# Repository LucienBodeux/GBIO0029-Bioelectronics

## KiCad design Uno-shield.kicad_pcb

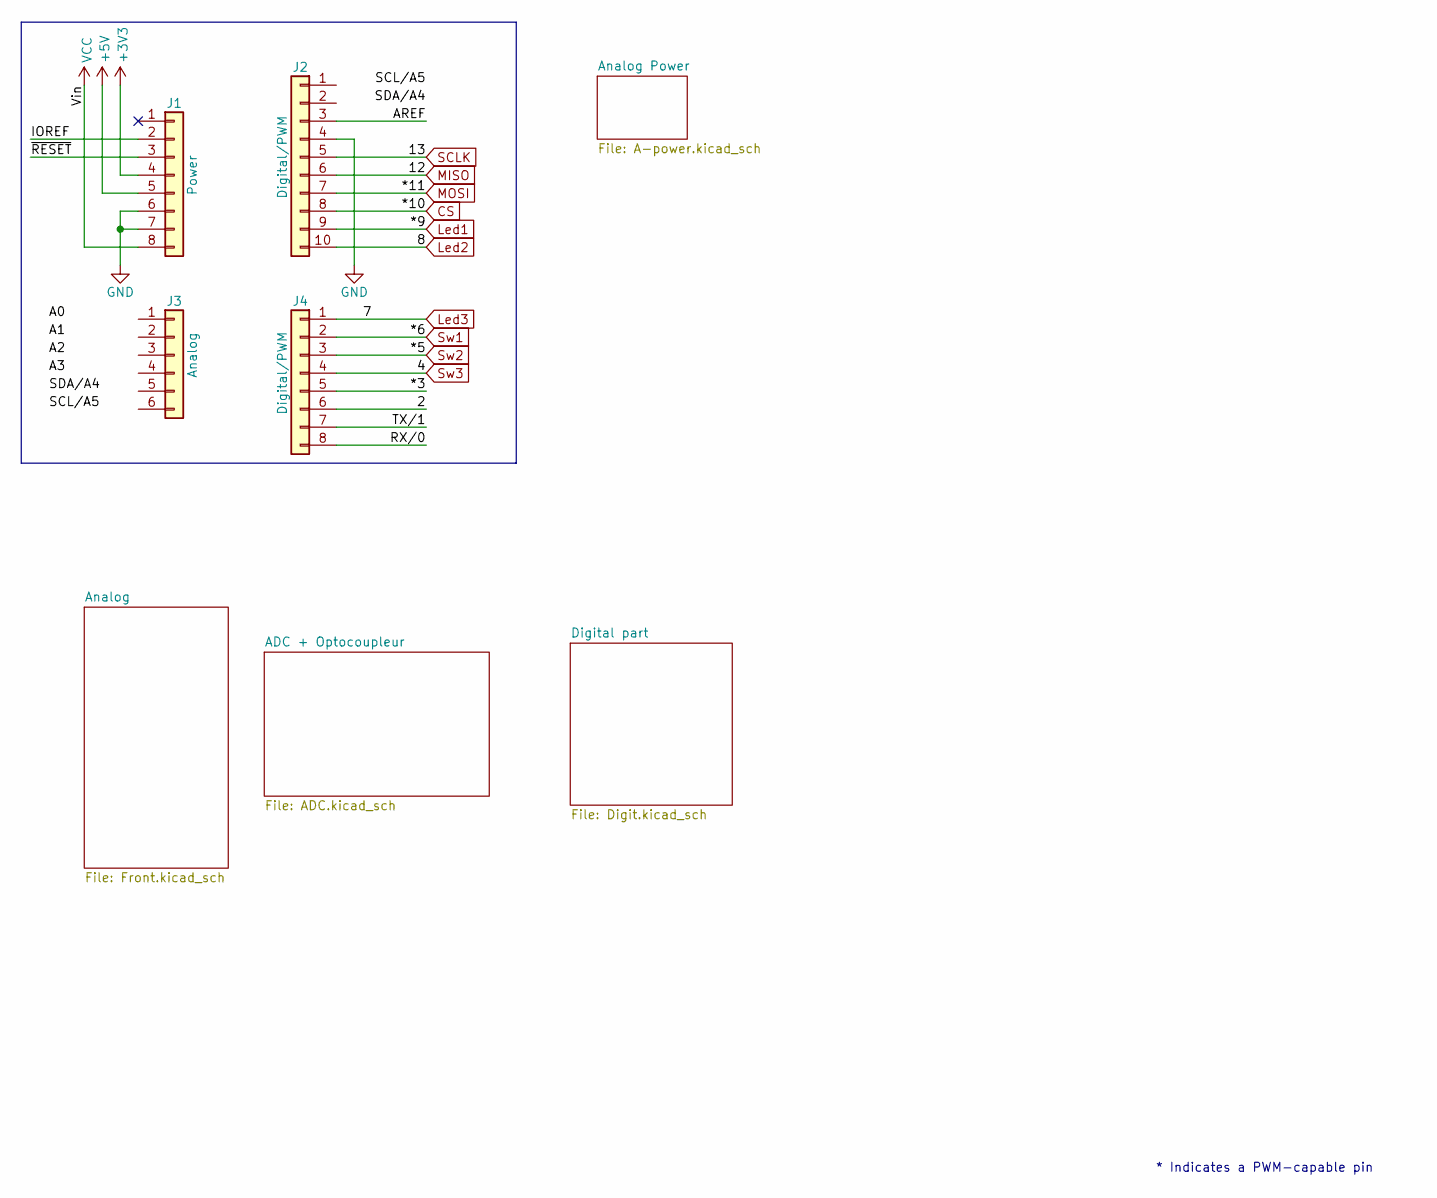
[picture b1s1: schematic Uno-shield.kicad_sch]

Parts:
J1: Power; PinSocket_1x08_P2.54mm_Vertical
J2: Digital/PWM; PinSocket_1x10_P2.54mm_Vertical
J3: Analog; PinSocket_1x06_P2.54mm_Vertical
J4: Digital/PWM; PinSocket_1x08_P2.54mm_Vertical

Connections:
+3V3: J1.4; also elsewhere on the board
+5V: J1.5; also elsewhere on the board
/2: J4.6
/*3: J4.5
/AREF: J2.3
/IOREF: J1.2
/RX/0: J4.8
/TX/1: J4.7
/~RESET: J1.3
CS: J2.8; also elsewhere on the board
GND: J1.6, J1.7, J2.4; also elsewhere on the board
Led1: J2.9; also elsewhere on the board
Led2: J2.10; also elsewhere on the board
Led3: J4.1; also elsewhere on the board
MISO: J2.6; also elsewhere on the board
MOSI: J2.7; also elsewhere on the board
SCLK: J2.5; also elsewhere on the board
Sw1: J4.2; also elsewhere on the board
Sw2: J4.3; also elsewhere on the board
Sw3: J4.4; also elsewhere on the board
VCC: J1.8

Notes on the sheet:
* Indicates a PWM-capable pin

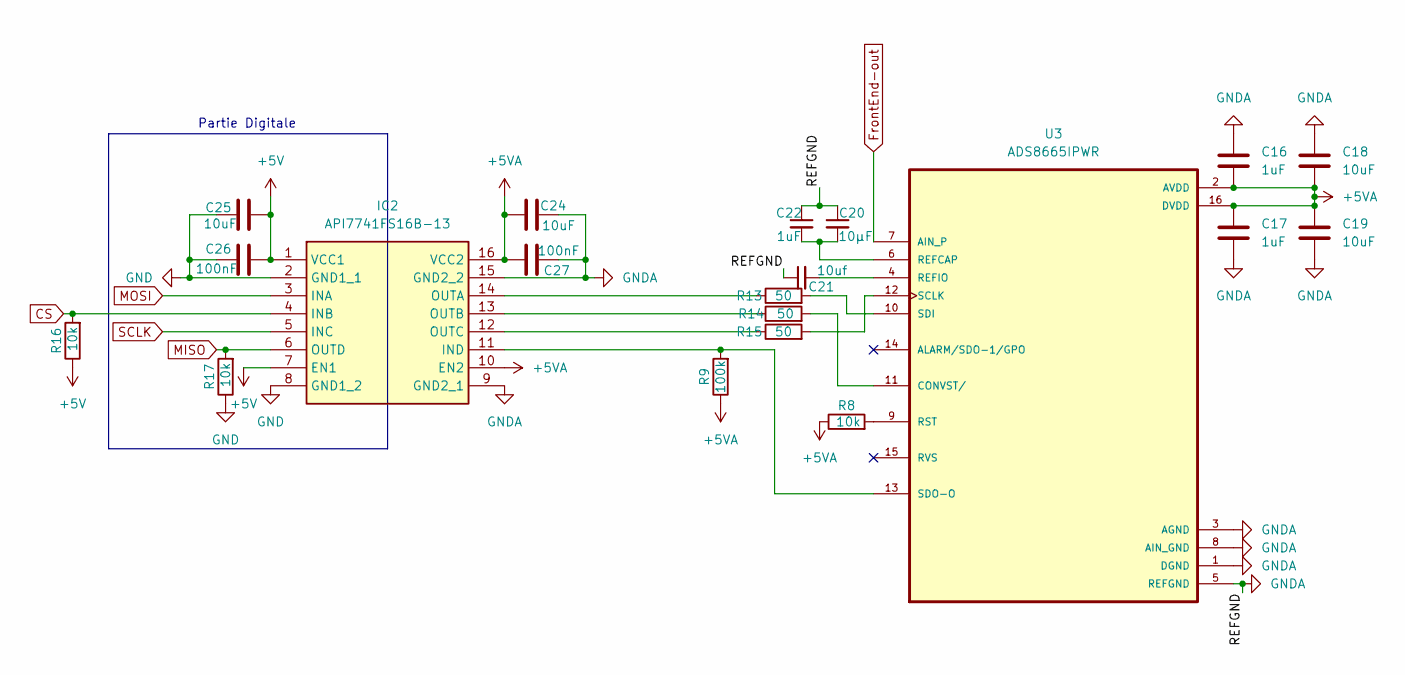
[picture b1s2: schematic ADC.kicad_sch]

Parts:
C16, C17, C22: 1uF; C_0805_2012Metric_Pad1.18x1.45mm_HandSolder
C18, C19, C24, C25: 10uF; C_1206_3216Metric_Pad1.33x1.80mm_HandSolder
C20: 10µF; C_1206_3216Metric_Pad1.33x1.80mm_HandSolder
C21: 10uf; C_1206_3216Metric_Pad1.33x1.80mm_HandSolder
C26, C27: 100nF; C_0805_2012Metric_Pad1.18x1.45mm_HandSolder
IC2: API7741FS16B-13; SOIC-16W_7.5x10.3mm_P1.27mm; Manufacturer_Part_Number API7741FS16B-13
R8, R16, R17: 10k; R_0805_2012Metric_Pad1.20x1.40mm_HandSolder
R9: 100k; R_0805_2012Metric_Pad1.20x1.40mm_HandSolder
R13, R14, R15: 50; R_0805_2012Metric_Pad1.20x1.40mm_HandSolder
U3: ADS8665IPWR; TSSOP-16_4.4x5mm_P0.65mm; MPN ADS8665IPWR

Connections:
+5V: C25.2, C26.2, IC2.1 (VCC1), IC2.7 (EN1), R16.1; also elsewhere on the board
+5VA: C16.2, C17.1, C18.2, C19.1, C24.1, C27.2, IC2.10 (EN2), IC2.16 (VCC2), R8.1, R9.1, U3.2 (AVDD), U3.16 (DVDD); also elsewhere on the board
CS: IC2.4 (INB), R16.2; also elsewhere on the board
FrontEnd-out: U3.7 (AIN_P); also elsewhere on the board
GND: C25.1, C26.1, IC2.2 (GND1_1), IC2.8 (GND1_2), R17.1; also elsewhere on the board
GNDA: C16.1, C17.2, C18.1, C19.2, C20.1, C21.1, C22.1, C24.2, C27.1, IC2.9 (GND2_1), IC2.15 (GND2_2), U3.1 (DGND), U3.3 (AGND), U3.5 (REFGND), U3.8 (AIN_GND); also elsewhere on the board
MISO: IC2.6 (OUTD), R17.2; also elsewhere on the board
MOSI: IC2.3 (INA); also elsewhere on the board
unnamed: IC2.11 (IND), R9.2, U3.13 (SDO-O)
unnamed: IC2.14 (OUTA), R13.1
unnamed: IC2.13 (OUTB), R14.1
unnamed: IC2.12 (OUTC), R15.1
unnamed: R14.2, U3.11 (CONVST/)
unnamed: C20.2, C22.2, U3.6 (REFCAP)
unnamed: C21.2, U3.4 (REFIO)
unnamed: R8.2, U3.9 (RST)
unnamed: R15.2, U3.12 (SCLK)
unnamed: R13.2, U3.10 (SDI)
SCLK: IC2.5 (INC); also elsewhere on the board

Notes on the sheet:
Partie Digitale

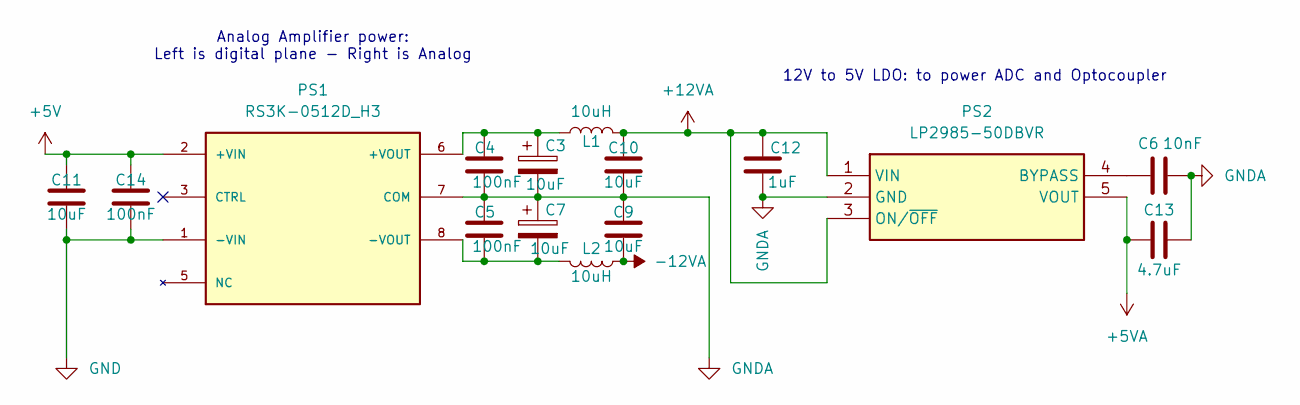
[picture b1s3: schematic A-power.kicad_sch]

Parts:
C3, C7, C9, C10, C11: 10uF; C_1206_3216Metric_Pad1.33x1.80mm_HandSolder
C4, C5, C14: 100nF; C_0805_2012Metric_Pad1.18x1.45mm_HandSolder
C6: 10nF; C_0805_2012Metric_Pad1.18x1.45mm_HandSolder
C12: 1uF; C_0805_2012Metric_Pad1.18x1.45mm_HandSolder
C13: 4.7uF; C_0805_2012Metric_Pad1.18x1.45mm_HandSolder
L1, L2: 10uH; L_Bourns-SRN4018
PS1: RS3K-0512D_H3; Converter_DCDC_TRACO_TEC2-12xxWI_24xxWI_48xxWI_THT; MPN RS3K-0512D/H3; DigiKey_Part_Number 945-RS3K-0512D/H3-ND
PS2: LP2985-50DBVR; SOT-23-5_HandSoldering; Mouser Part Number 595-LP2985-50DBVR

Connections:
+5V: C11.1, C14.1, PS1.2 (+VIN); also elsewhere on the board
+5VA: C13.1, PS2.5 (VOUT); also elsewhere on the board
+12VA: C10.1, C12.1, L1.2, PS2.1 (VIN), PS2.3 (ON/~OFF); also elsewhere on the board
-12VA: C9.2, L2.1; also elsewhere on the board
GND: C11.2, C14.2, PS1.1 (-VIN); also elsewhere on the board
GNDA: C3.2, C4.1, C5.2, C6.2, C7.1, C9.1, C10.2, C12.2, C13.2, PS1.7 (COM), PS2.2 (GND); also elsewhere on the board
unnamed: C3.1, C4.2, L1.1, PS1.6 (+VOUT)
unnamed: C5.1, C7.2, L2.2, PS1.8 (-VOUT)
unnamed: C6.1, PS2.4 (BYPASS)

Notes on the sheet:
12V to 5V LDO: to power ADC and Optocoupler
Analog Amplifier power: Left is digital plane - Right is Analog

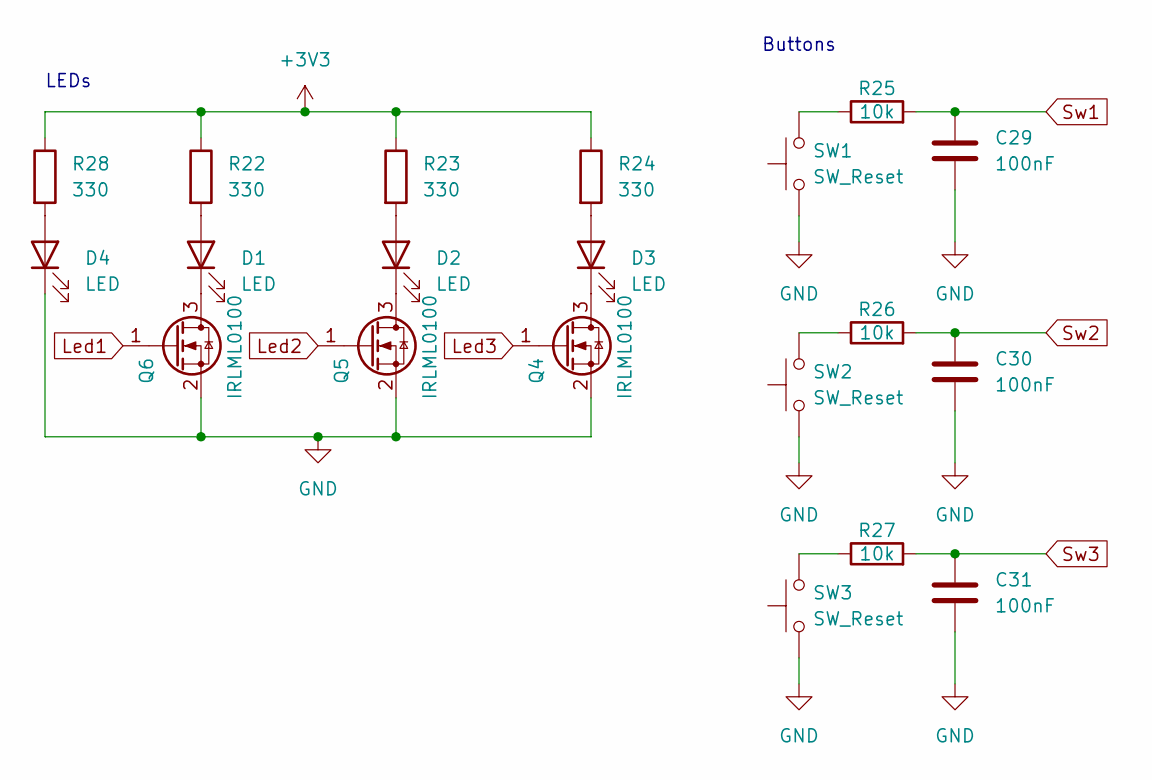
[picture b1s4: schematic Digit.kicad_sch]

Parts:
C29, C30, C31: 100nF; C_0805_2012Metric_Pad1.18x1.45mm_HandSolder
D1, D2, D3, D4: LED; LED_0805_2012Metric_Pad1.15x1.40mm_HandSolder
Q4, Q5, Q6: IRLML0100; SOT-23
R22, R23, R24, R28: 330; R_0805_2012Metric_Pad1.20x1.40mm_HandSolder
R25, R26, R27: 10k; R_0805_2012Metric_Pad1.20x1.40mm_HandSolder
SW1, SW2, SW3: SW_Reset; SW_PUSH_6mm

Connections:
+3V3: R22.1, R23.1, R24.1, R28.1; also elsewhere on the board
GND: C29.2, C30.2, C31.2, D4.1 (K), Q4.2 (S), Q5.2 (S), Q6.2 (S), SW1.1, SW2.1, SW3.1; also elsewhere on the board
Led1: Q6.1 (G); also elsewhere on the board
Led2: Q5.1 (G); also elsewhere on the board
Led3: Q4.1 (G); also elsewhere on the board
unnamed: D1.2 (A), R22.2
unnamed: D1.1 (K), Q6.3 (D)
unnamed: D2.2 (A), R23.2
unnamed: D2.1 (K), Q5.3 (D)
unnamed: D3.2 (A), R24.2
unnamed: D3.1 (K), Q4.3 (D)
unnamed: D4.2 (A), R28.2
unnamed: R25.1, SW1.2
unnamed: R26.1, SW2.2
unnamed: R27.1, SW3.2
Sw1: C29.1, R25.2; also elsewhere on the board
Sw2: C30.1, R26.2; also elsewhere on the board
Sw3: C31.1, R27.2; also elsewhere on the board

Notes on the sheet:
LEDs
Buttons

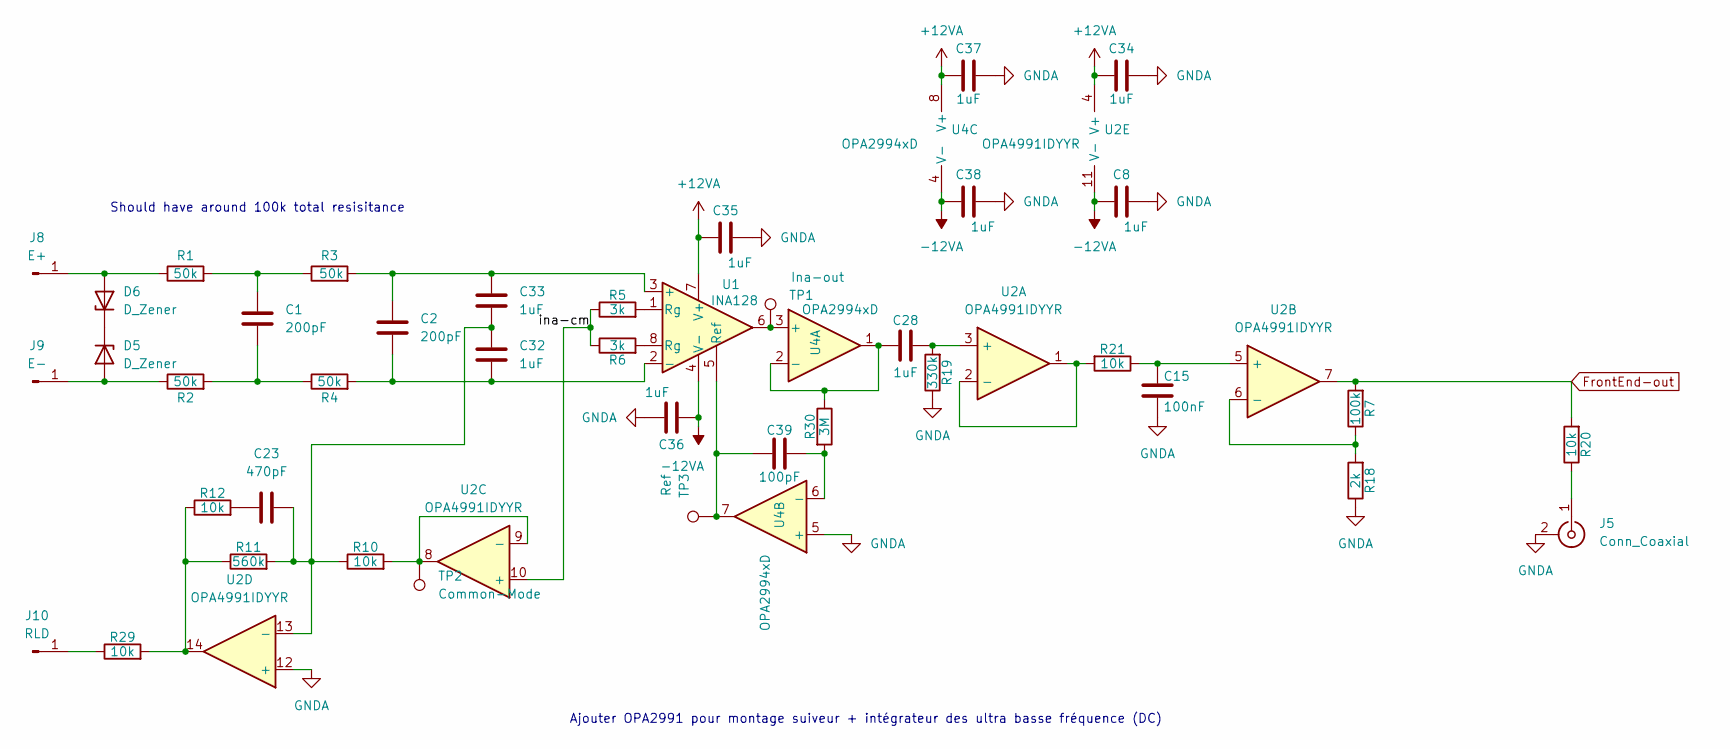
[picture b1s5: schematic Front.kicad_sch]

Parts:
C1, C2: 200pF; C_0805_2012Metric_Pad1.18x1.45mm_HandSolder
C8, C28, C32, C33, C34, C35, C36, C37, C38: 1uF; C_0805_2012Metric_Pad1.18x1.45mm_HandSolder
C15: 100nF; C_1206_3216Metric_Pad1.33x1.80mm_HandSolder
C23: 470pF; C_0805_2012Metric_Pad1.18x1.45mm_HandSolder
C39: 100pF; C_0805_2012Metric_Pad1.18x1.45mm_HandSolder
D5, D6: D_Zener; D_SMA_Handsoldering
J5: Conn_Coaxial; 031532951RFX
J8: E+; MountingHole_3.5mm_Pad_TopOnly
J9: E-; MountingHole_3.5mm_Pad_TopOnly
J10: RLD; MountingHole_3.5mm_Pad_TopOnly
R1, R2, R3, R4: 50k; R_0805_2012Metric_Pad1.20x1.40mm_HandSolder
R5, R6: 3k; R_0805_2012Metric_Pad1.20x1.40mm_HandSolder
R7: 100k; R_0805_2012Metric_Pad1.20x1.40mm_HandSolder
R10, R12, R20, R21, R29: 10k; R_0805_2012Metric_Pad1.20x1.40mm_HandSolder
R11: 560k; R_0805_2012Metric_Pad1.20x1.40mm_HandSolder
R18: 2k; R_0805_2012Metric_Pad1.20x1.40mm_HandSolder
R19: 330k; R_0805_2012Metric_Pad1.20x1.40mm_HandSolder
R30: 3M; R_0805_2012Metric_Pad1.20x1.40mm_HandSolder
TP1: Ina-out; TestPoint_Pad_D2.0mm
TP2: Common-Mode; TestPoint_Pad_D2.0mm
TP3: Ref; TestPoint_Pad_D2.0mm
U1: INA128; SOIC-8_3.9x4.9mm_P1.27mm
U2: OPA4991IDYYR; SOIC-14_3.9x8.7mm_P1.27mm
U4: OPA2994xD; SOIC-8_3.9x4.9mm_P1.27mm

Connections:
+12VA: C34.1, C35.1, C37.1, U1.7 (V+), U2.4 (V+), U4.8 (V+); also elsewhere on the board
-12VA: C8.1, C36.1, C38.1, U1.4 (V-), U2.11 (V-), U4.4 (V-); also elsewhere on the board
/Analog/ina-cm: R5.1, R6.1, U2.10 (+)
FrontEnd-out: R7.2, R20.2, U2.7; also elsewhere on the board
GNDA: C8.2, C15.1, C34.2, C35.2, C36.2, C37.2, C38.2, J5.2 (Ext), R18.1, R19.1, U2.12 (+), U4.5 (+); also elsewhere on the board
unnamed: C1.1, R1.2, R3.1
unnamed: C1.2, R2.2, R4.1
unnamed: C23.2, R12.2
unnamed: D5.2 (A), J9.1 (Pin_1_1), R2.1
unnamed: D5.1 (K), D6.1 (K)
unnamed: D6.2 (A), J8.1 (Pin_1_1), R1.1
unnamed: J5.1 (In), R20.1
unnamed: J10.1 (Pin_1_1), R29.1
unnamed: R5.2, U1.1 (Rg)
unnamed: R6.2, U1.8 (Rg)
unnamed: R11.1, R12.1, R29.2, U2.14
unnamed: C2.1, C33.1, R3.2, U1.3 (+)
unnamed: C2.2, C32.2, R4.2, U1.2 (-)
unnamed: C39.1, TP3.1 (1_1), U1.5 (Ref), U4.7
unnamed: C28.2, R19.2, U2.3 (+)
unnamed: R21.2, U2.1, U2.2 (-)
unnamed: C15.2, R21.1, U2.5 (+)
unnamed: R7.1, R18.2, U2.6 (-)
unnamed: R10.2, TP2.1 (1_1), U2.8, U2.9 (-)
unnamed: C23.1, C32.1, C33.2, R10.1, R11.2, U2.13 (-)
unnamed: TP1.1 (1_1), U1.6, U4.3 (+)
unnamed: C28.1, R30.1, U4.1, U4.2 (-)
unnamed: C39.2, R30.2, U4.6 (-)

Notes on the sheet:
Ajouter OPA2991 pour montage suiveur + intégrateur des ultra basse fréquence (DC)
Should have around 100k total resisitance

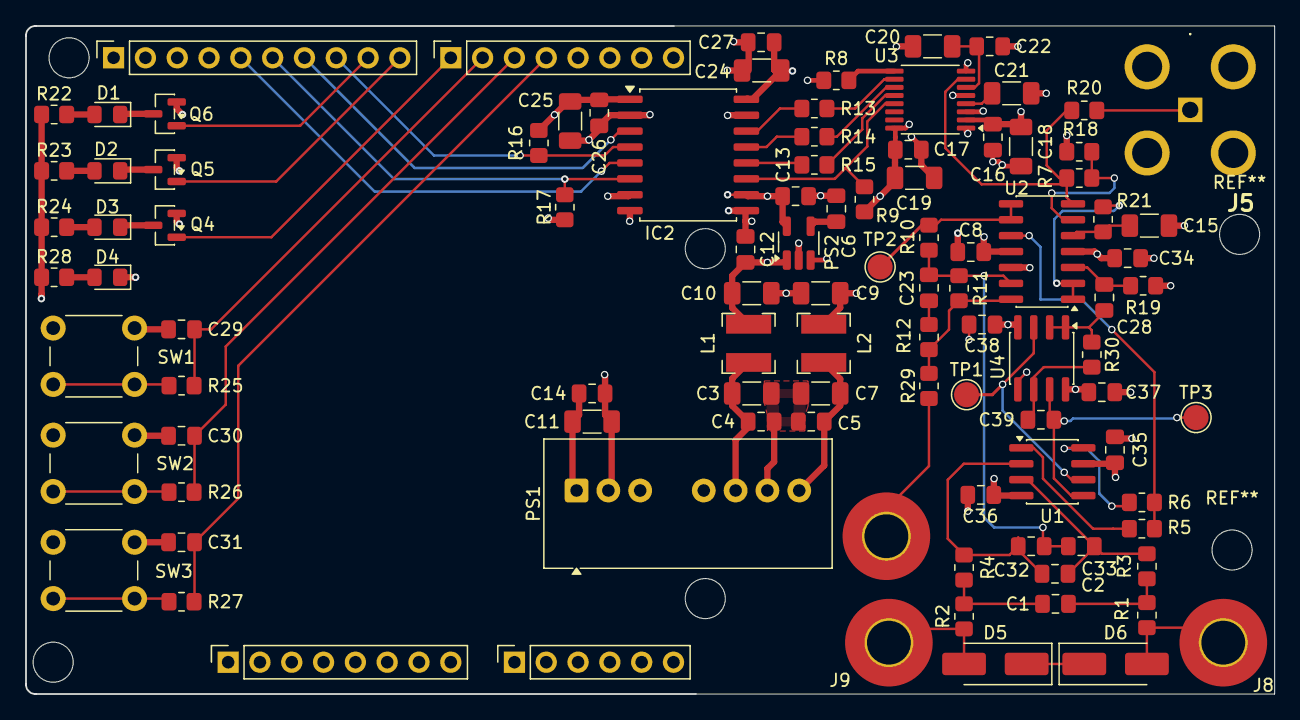
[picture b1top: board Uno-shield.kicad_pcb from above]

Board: 4 copper layers, 99.7 x 53.3 mm, 105 parts (0 on the bottom side), 65 nets.

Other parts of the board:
MH1, MH2, MH3, MH4: MountingHole_3.2mm

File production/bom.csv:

Designator,Footprint,Quantity,Value,LCSC Part #
"C1, C2",0805,2,200pF,
"C10, C11, C18, C19, C21, C24, C25, C3, C7, C9",1206,10,10uF,
"C12, C16, C17, C22, C28, C32, C33, C34, C35, C36, C37, C38, C8",0805,13,1uF,
C13,0805,1,4.7uF,
"C14, C26, C27, C29, C30, C31, C4, C5",0805,8,100nF,
C15,1206,1,100nF,
C20,1206,1,10µF,
C23,0805,1,470pF,
C39,0805,1,100pF,
C6,0805,1,10nF,
"D1, D2, D3, D4",0805,4,LED,
"D5, D6",D_SMA_Handsoldering,2,D_Zener,
IC2,SOIC-16W_7.5x10.3mm_P1.27mm,1,API7741FS16B-13,
J1,PinSocket_1x08_P2.54mm_Vertical,1,Power,
J10,MountingHole_3.5mm_Pad_TopOnly,1,RLD,
J2,PinSocket_1x10_P2.54mm_Vertical,1,Digital/PWM,
J3,PinSocket_1x06_P2.54mm_Vertical,1,Analog,
J4,PinSocket_1x08_P2.54mm_Vertical,1,Digital/PWM,
J5,031532951RFX,1,Conn_Coaxial,
J8,MountingHole_3.5mm_Pad_TopOnly,1,E+,
J9,MountingHole_3.5mm_Pad_TopOnly,1,E-,
"L1, L2",L_Bourns-SRN4018,2,10uH,
PS1,Converter_DCDC_TRACO_TEC2-12xxWI_24xxWI_48xxWI_THT,1,RS3K-0512D_H3,RS3K-0512D/H3
PS2,SOT-23-5_HandSoldering,1,LP2985-50DBVR,
"Q4, Q5, Q6",SOT-23,3,IRLML0100,
"R1, R2, R3, R4",0805,4,50k,
"R10, R12, R16, R17, R20, R21, R25, R26, R27, R29, R8",0805,11,10k,
R11,0805,1,560k,
"R13, R14, R15",0805,3,50,
R18,0805,1,2k,
R19,0805,1,330k,
"R22, R23, R24, R28",0805,4,330,
R30,0805,1,3M,
"R5, R6",0805,2,3k,
"R7, R9",0805,2,100k,
"SW1, SW2, SW3",SW_PUSH_6mm,3,SW_Reset,
U1,SOIC-8_3.9x4.9mm_P1.27mm,1,INA128,
U2,SOIC-14_3.9x8.7mm_P1.27mm,1,OPA4991IDYYR,
U3,TSSOP-16_4.4x5mm_P0.65mm,1,ADS8665IPWR,ADS8665IPWR
U4,SOIC-8_3.9x4.9mm_P1.27mm,1,OPA2994xD,
